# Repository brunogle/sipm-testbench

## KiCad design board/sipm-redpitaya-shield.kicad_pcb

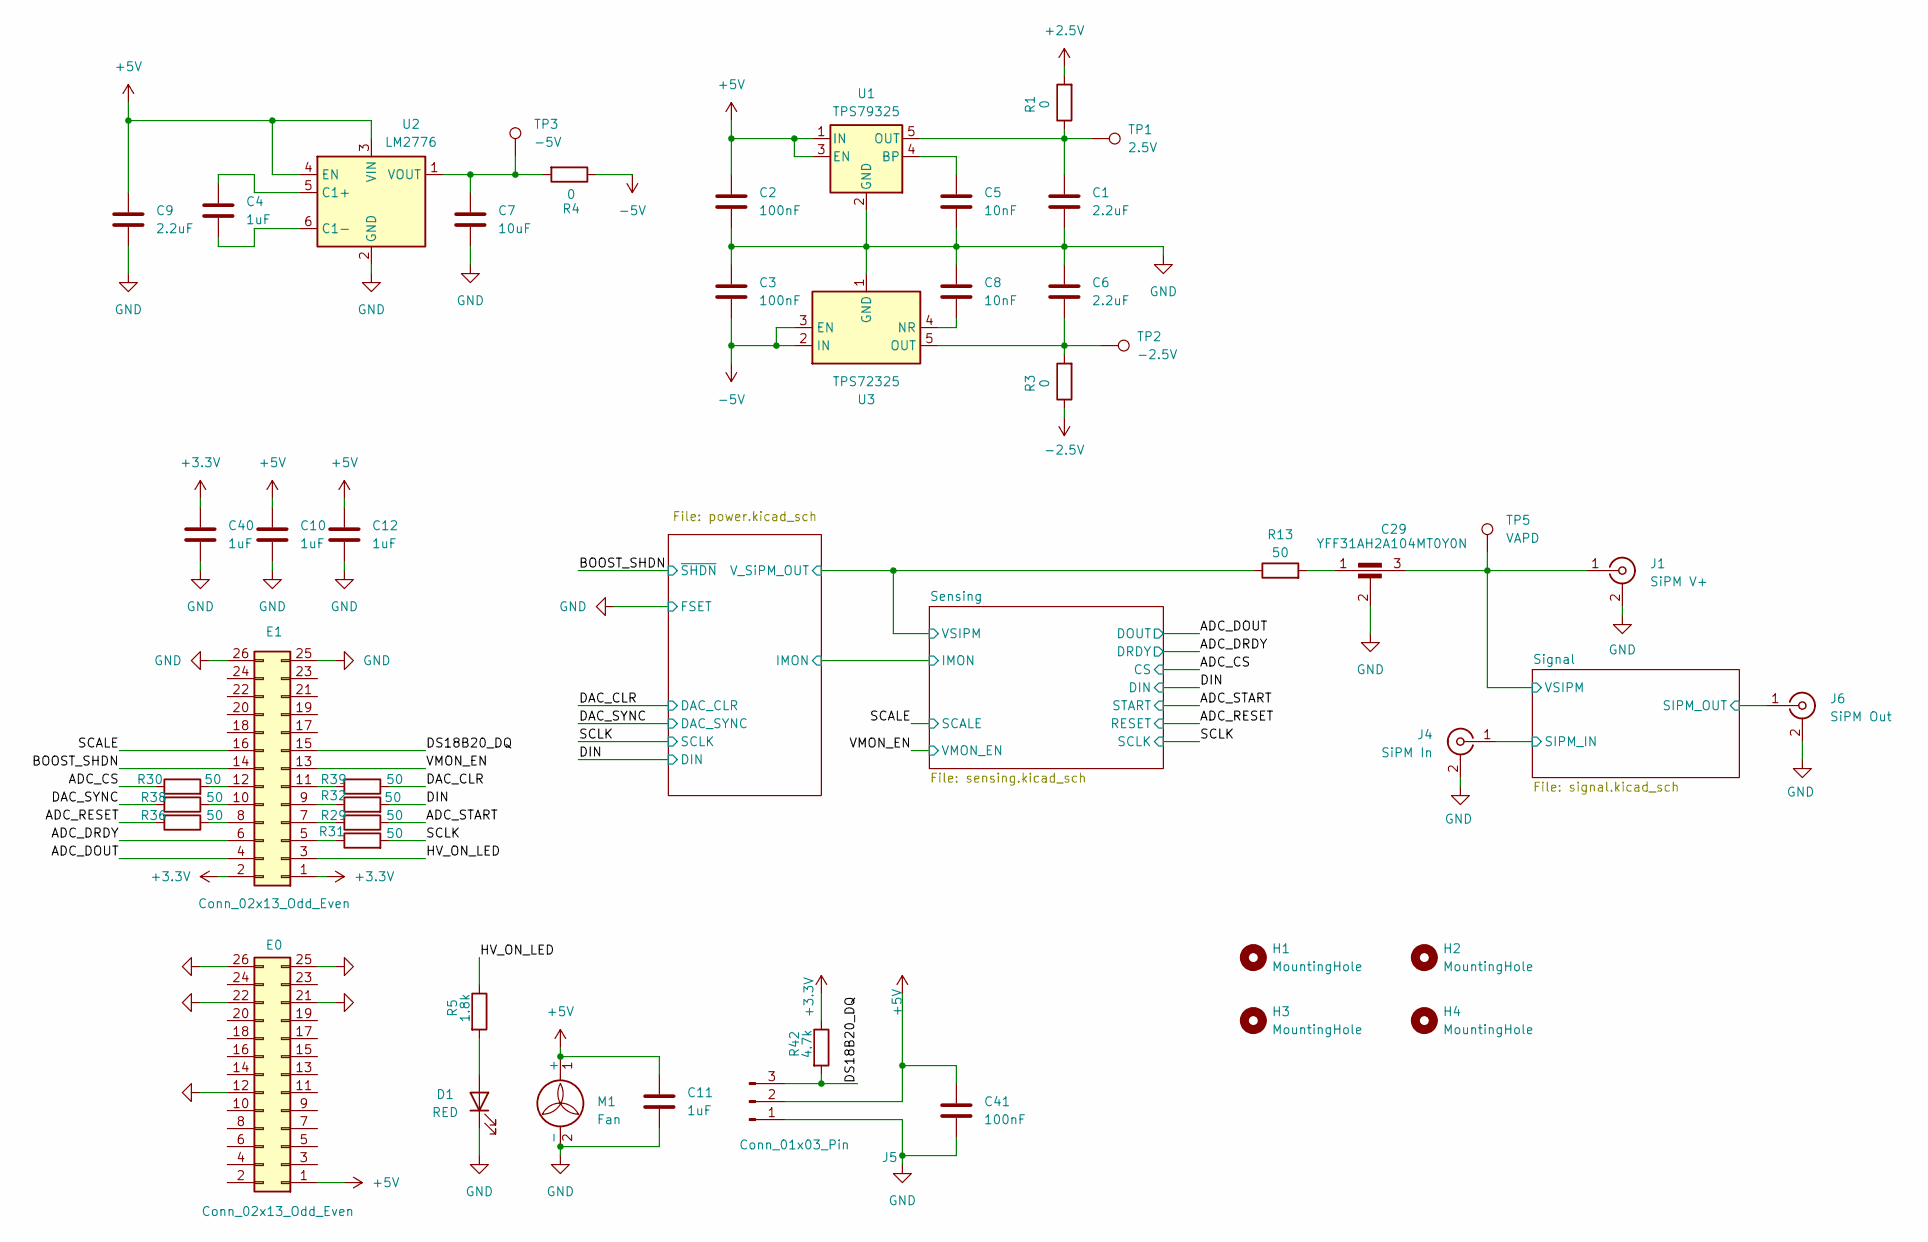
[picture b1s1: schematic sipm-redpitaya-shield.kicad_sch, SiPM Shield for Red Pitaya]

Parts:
C1, C6, C9: 2.2uF; C_0603_1608Metric
C2, C3, C41: 100nF; C_0603_1608Metric
C4, C10, C11, C12, C40: 1uF; C_0603_1608Metric
C5, C8: 10nF; C_0603_1608Metric
C7: 10uF; C_0603_1608Metric
C29: YFF31AH2A104MT0Y0N; YFF31HC
D1: RED; LED_0603_1608Metric_Pad1.05x0.95mm_HandSolder
E0, E1: Conn_02x13_Odd_Even; PinSocket_2x13_P2.54mm_Vertical
H1, H2, H3, H4: MountingHole; JLCPCB_ToolingHole
J1: SiPM V+; SMA_Samtec_SMA-J-P-H-ST-EM1_EdgeMount
J4: SiPM In; SMA_Samtec_SMA-J-P-H-ST-EM1_EdgeMount
J5: Conn_01x03_Pin; Molex_KK-254_AE-6410-03A_1x03_P2.54mm_Vertical
J6: SiPM Out; SMA_Samtec_SMA-J-P-H-ST-EM1_EdgeMount
M1: Fan; PinHeader_1x02_P2.54mm_Vertical
R1, R3, R4: 0; R_0603_1608Metric_Pad0.98x0.95mm_HandSolder
R5: 1.8k; R_0603_1608Metric
R13: 50; R_0603_1608Metric
R29, R30, R31, R32, R36, R38, R39: 50; R_0402_1005Metric
R42: 4.7k; R_0603_1608Metric
TP1: 2.5V; TestPoint_Pad_D1.0mm
TP2: -2.5V; TestPoint_Pad_D1.0mm
TP3: -5V; TestPoint_Pad_D1.0mm
TP5: VAPD; TestPoint_Pad_D1.0mm
U1: TPS79325; SOT-23-5
U2: LM2776; SOT-23-6
U3: TPS72325; SOT-23-5

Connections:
+2.5V: R1.2; also elsewhere on the board
+3.3V: C40.2, E1.1, E1.2, R42.1; also elsewhere on the board
+5V: C2.1, C9.1, C10.2, C11.1, C12.2, C41.2, E0.1, J5.2, M1.1 (+), U1.1 (IN), U1.3 (EN), U2.3 (VIN), U2.4 (EN); also elsewhere on the board
-2.5V: R3.1; also elsewhere on the board
-5V: C3.2, R4.1, U3.2 (IN), U3.3 (EN)
/ADC_CS: R30.1; also elsewhere on the board
/ADC_DOUT: E1.4; also elsewhere on the board
/ADC_DRDY: E1.6; also elsewhere on the board
/ADC_RESET: R36.2; also elsewhere on the board
/ADC_START: R29.1; also elsewhere on the board
/BOOST_SHDN: E1.14; also elsewhere on the board
/DAC_CLR: R39.1; also elsewhere on the board
/DAC_SYNC: R38.2; also elsewhere on the board
/DIN: R32.2; also elsewhere on the board
/DS18B20_DQ: E1.15, J5.3, R42.2
/HV_ON_LED: E1.3, R5.1
/Power/V_SiPM_OUT: R13.1; also elsewhere on the board
/SCALE: E1.16; also elsewhere on the board
/SCLK: R31.2; also elsewhere on the board
/Signal/SIPM_IN: J4.1 (In); also elsewhere on the board
/Signal/SIPM_OUT: J6.1 (In); also elsewhere on the board
/Signal/VSIPM: C29.3, J1.1 (In), TP5.1; also elsewhere on the board
/VMON_EN: E1.13; also elsewhere on the board
GND: C1.2, C2.2, C3.1, C5.2, C6.1, C7.2, C8.1, C9.2, C10.1, C11.2, C12.1, C29.2, C40.1, C41.1, D1.1 (K), E0.12, E0.21, E0.22, E0.25, E0.26, E1.25, E1.26, J1.2 (Ext), J4.2 (Ext), J5.1, J6.2 (Ext), M1.2 (-), U1.2 (GND), U2.2 (GND), U3.1 (GND); also elsewhere on the board
unnamed: C29.1, R13.2
unnamed: D1.2 (A), R5.2
unnamed: E1.5, R31.1
unnamed: E1.7, R29.2
unnamed: E1.8, R36.1
unnamed: E1.9, R32.1
unnamed: E1.10, R38.1
unnamed: E1.11, R39.2
unnamed: E1.12, R30.2
unnamed: C5.1, U1.4 (BP)
unnamed: C1.1, R1.1, TP1.1, U1.5 (OUT)
unnamed: C4.1, U2.5 (C1+)
unnamed: C4.2, U2.6 (C1-)
unnamed: C7.1, R4.2, TP3.1, U2.1 (VOUT)
unnamed: C8.2, U3.4 (NR)
unnamed: C6.2, R3.2, TP2.1, U3.5 (OUT)

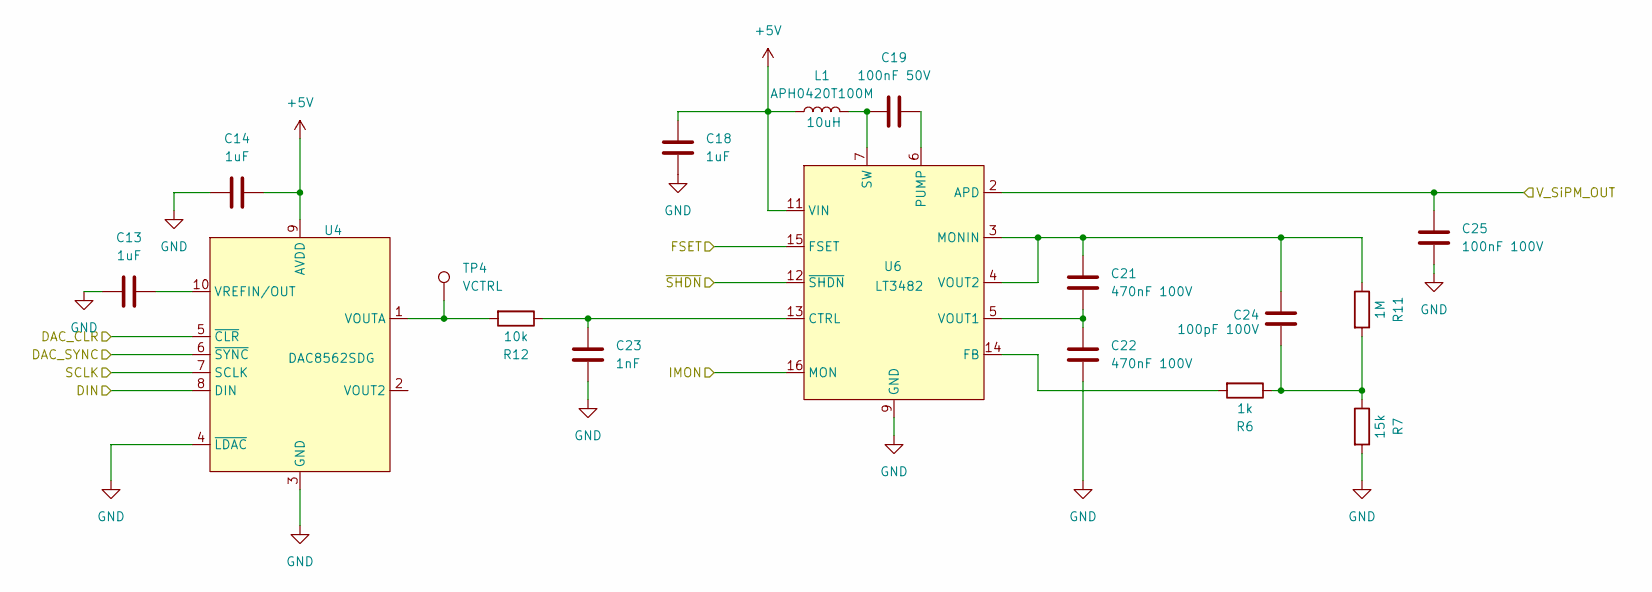
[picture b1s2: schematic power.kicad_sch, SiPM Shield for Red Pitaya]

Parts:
C13, C14, C18: 1uF; C_0603_1608Metric
C19: 100nF 50V; C_0603_1608Metric
C21, C22: 470nF 100V; C_1206_3216Metric
C23: 1nF; C_0603_1608Metric
C24: 100pF 100V; C_0603_1608Metric
C25: 100nF 100V; C_0805_2012Metric
L1: APH0420T100M; L_APV_APH0420
R6: 1k; R_0603_1608Metric
R7: 15k; R_0603_1608Metric
R11: 1M; R_0603_1608Metric
R12: 10k; R_0603_1608Metric
TP4: VCTRL; TestPoint_Pad_D1.0mm
U4: DAC8562SDG; VSSOP-10_3x3mm_P0.5mm
U6: LT3482; QFN-16-1EP_3x3mm_P0.5mm_EP1.45x1.45mm

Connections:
+5V: C14.2, C18.1, L1.1, U4.9 (AVDD), U6.11 (VIN); also elsewhere on the board
/BOOST_SHDN: U6.12 (~SHDN); also elsewhere on the board
/DAC_CLR: U4.5 (~CLR); also elsewhere on the board
/DAC_SYNC: U4.6 (~SYNC); also elsewhere on the board
/DIN: U4.8 (DIN); also elsewhere on the board
/Power/IMON: U6.16 (MON); also elsewhere on the board
/Power/V_SiPM_OUT: C25.1, U6.2 (APD); also elsewhere on the board
/SCLK: U4.7 (SCLK); also elsewhere on the board
GND: C13.2, C14.1, C18.2, C22.2, C23.1, C25.2, R7.2, U4.3 (GND), U4.4 (~LDAC), U6.9 (GND), U6.10 (GND), U6.15 (FSET), U6.17 (GND); also elsewhere on the board
unnamed: C19.2, L1.2, U6.7 (SW), U6.8 (SW)
unnamed: C24.2, R6.1, R7.1, R11.2
unnamed: R12.2, TP4.1, U4.1 (VOUTA)
unnamed: C13.1, U4.10 (VREFIN/OUT)
unnamed: C23.2, R12.1, U6.13 (CTRL)
unnamed: R6.2, U6.14 (FB)
unnamed: C21.1, C24.1, R11.1, U6.3 (MONIN), U6.4 (VOUT2)
unnamed: C19.1, U6.6 (PUMP)
unnamed: C21.2, C22.1, U6.5 (VOUT1)

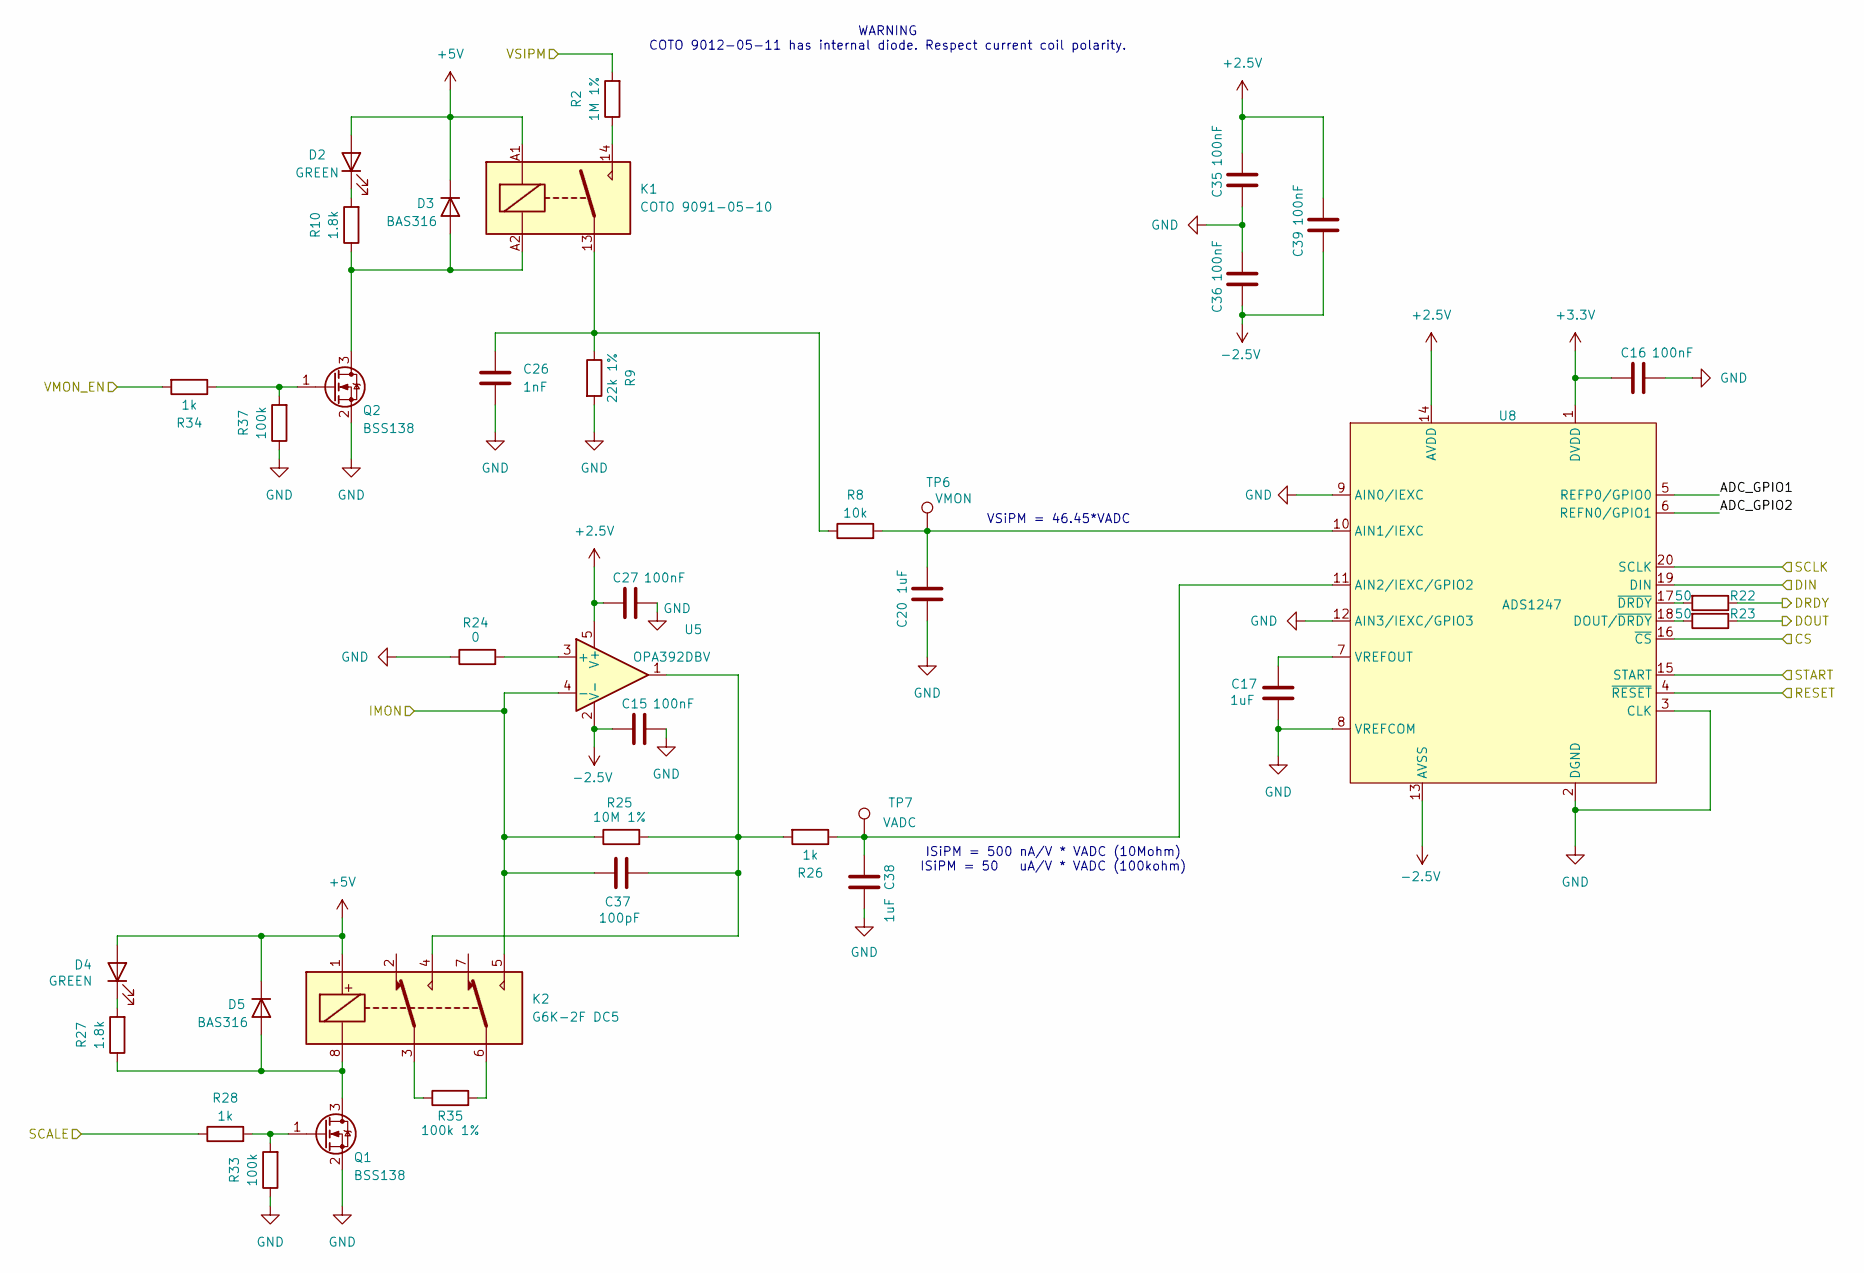
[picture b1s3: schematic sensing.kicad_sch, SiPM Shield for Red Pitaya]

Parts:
C15, C16, C27, C35, C36, C39: 100nF; C_0603_1608Metric
C17, C20, C38: 1uF; C_0603_1608Metric
C26: 1nF; C_0603_1608Metric
C37: 100pF; C_0603_1608Metric_Pad1.08x0.95mm_HandSolder
D2, D4: GREEN; LED_0603_1608Metric_Pad1.05x0.95mm_HandSolder
D3, D5: BAS316; D_SOD-323
K1: COTO 9091-05-10; Relay_SPST_COTO_9091
K2: G6K-2F DC5; Relay_DPDT_Omron_G6K-2F
Q1, Q2: BSS138; SOT-23
R2: 1M 1%; R_0603_1608Metric
R8: 10k; R_0603_1608Metric
R9: 22k 1%; R_0603_1608Metric
R10, R27: 1.8k; R_0603_1608Metric
R22, R23: 50; R_0603_1608Metric
R24: 0; R_0603_1608Metric_Pad0.98x0.95mm_HandSolder
R25: 10M 1%; R_0603_1608Metric_Pad0.98x0.95mm_HandSolder
R26: 1k; R_0603_1608Metric
R28, R34: 1k; R_0402_1005Metric
R33, R37: 100k; R_0402_1005Metric
R35: 100k 1%; R_0603_1608Metric_Pad0.98x0.95mm_HandSolder
TP6: VMON; TestPoint_Pad_D1.0mm
TP7: VADC; TestPoint_Pad_D1.0mm
U5: OPA392DBV; SOT-23-5
U8: ADS1247; TSSOP-20_4.4x6.5mm_P0.65mm

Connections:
+2.5V: C27.1, C35.2, C39.2, U5.5 (V+), U8.14 (AVDD); also elsewhere on the board
+3.3V: C16.1, U8.1 (DVDD); also elsewhere on the board
+5V: D2.2 (A), D3.1 (K), D4.2 (A), D5.1 (K), K1.A1, K2.1; also elsewhere on the board
-2.5V: C15.1, C36.1, C39.1, U5.2 (V-), U8.13 (AVSS); also elsewhere on the board
/ADC_CS: U8.16 (~CS); also elsewhere on the board
/ADC_DOUT: R23.1; also elsewhere on the board
/ADC_DRDY: R22.1; also elsewhere on the board
/ADC_RESET: U8.4 (~RESET); also elsewhere on the board
/ADC_START: U8.15 (START); also elsewhere on the board
/DIN: U8.19 (DIN); also elsewhere on the board
/Power/IMON: C37.2, K2.5, R25.1, U5.4 (-); also elsewhere on the board
/Power/V_SiPM_OUT: R2.2; also elsewhere on the board
/SCALE: R28.1; also elsewhere on the board
/SCLK: U8.20 (SCLK); also elsewhere on the board
/Sensing/ADC_GPIO1: U8.5 (REFP0/GPIO0)
/Sensing/ADC_GPIO2: U8.6 (REFN0/GPIO1)
/VMON_EN: R34.2; also elsewhere on the board
GND: C15.2, C16.2, C17.1, C20.1, C26.2, C27.2, C35.1, C36.2, C38.2, Q1.2 (S), Q2.2 (S), R9.2, R24.1, R33.1, R37.1, U8.2 (DGND), U8.3 (CLK), U8.8 (VREFCOM), U8.9 (AIN0/IEXC), U8.12 (AIN3/IEXC/GPIO3); also elsewhere on the board
unnamed: C26.1, K1.13, R8.1, R9.1
unnamed: C37.1, K2.4, R25.2, R26.2, U5.1
unnamed: D2.1 (K), R10.2
unnamed: D3.2 (A), K1.A2, Q2.3 (D), R10.1
unnamed: D4.1 (K), R27.2
unnamed: D5.2 (A), K2.8, Q1.3 (D), R27.1
unnamed: K1.14, R2.1
unnamed: K2.3, R35.1
unnamed: K2.6, R35.2
unnamed: Q1.1 (G), R28.2, R33.2
unnamed: Q2.1 (G), R34.1, R37.2
unnamed: R24.2, U5.3 (+)
unnamed: C20.2, R8.2, TP6.1, U8.10 (AIN1/IEXC)
unnamed: C38.1, R26.1, TP7.1, U8.11 (AIN2/IEXC/GPIO2)
unnamed: R23.2, U8.18 (DOUT/~DRDY)
unnamed: C17.2, U8.7 (VREFOUT)
unnamed: R22.2, U8.17 (~DRDY)

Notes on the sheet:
ISiPM = 500 nA/V * VADC (10Mohm) ISiPM = 50 uA/V * VADC (100kohm)
VSiPM = 46.45*VADC
WARNING COTO 9012-05-11 has internal diode. Respect current coil polarity.

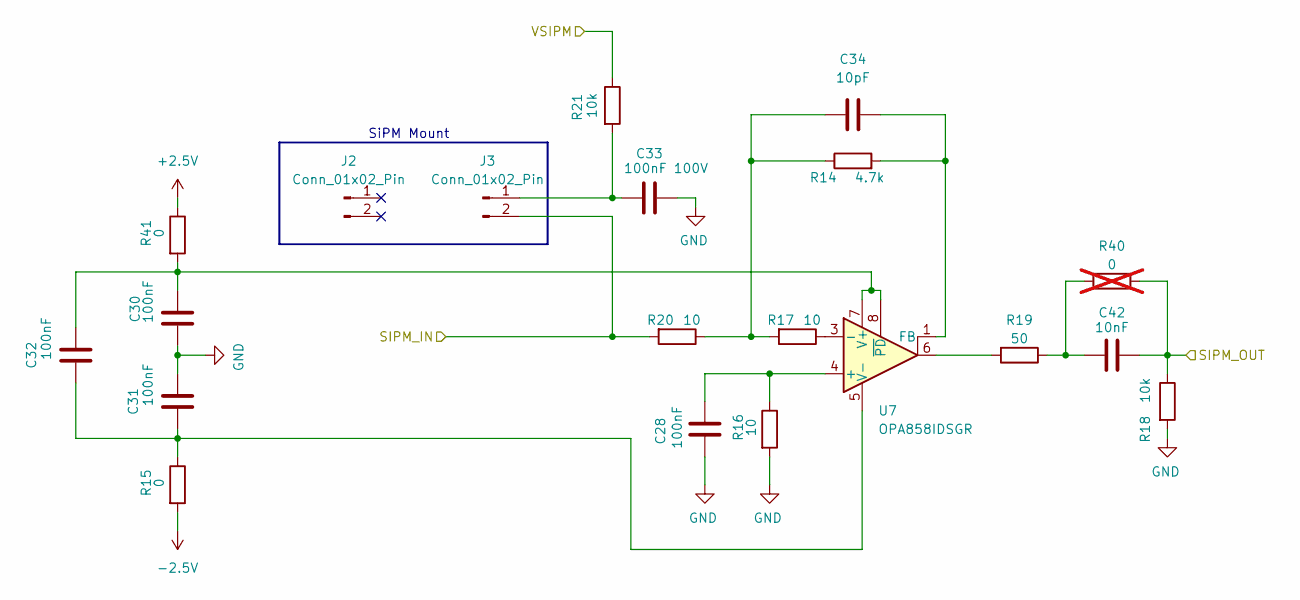
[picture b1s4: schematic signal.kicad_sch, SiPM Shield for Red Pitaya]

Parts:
C28, C30, C31, C32: 100nF; C_0603_1608Metric
C33: 100nF 100V; C_0805_2012Metric
C34: 10pF; C_0402_1005Metric_Pad0.74x0.62mm_HandSolder
C42: 10nF; C_0603_1608Metric
J2, J3: Conn_01x02_Pin; PinSocket_1x02_P2.54mm_Vertical
R14: 4.7k; R_0402_1005Metric_Pad0.72x0.64mm_HandSolder
R15, R41: 0; R_0603_1608Metric_Pad0.98x0.95mm_HandSolder
R16: 10; R_0603_1608Metric
R17, R20: 10; R_0402_1005Metric_Pad0.72x0.64mm_HandSolder
R18, R21: 10k; R_0603_1608Metric
R19: 50; R_0603_1608Metric
R40: 0; R_0603_1608Metric; not fitted
U7: OPA858IDSGR; WSON-8-1EP_2x2mm_P0.5mm_EP0.9x1.6mm

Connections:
+2.5V: R41.1; also elsewhere on the board
-2.5V: R15.2; also elsewhere on the board
/Signal/SIPM_IN: J3.2, R20.2; also elsewhere on the board
/Signal/SIPM_OUT: C42.2, R18.1, R40.1; also elsewhere on the board
/Signal/VSIPM: R21.1; also elsewhere on the board
GND: C28.1, C30.1, C31.2, C33.2, R16.2, R18.2; also elsewhere on the board
unnamed: C31.1, C32.1, R15.1, U7.5 (V-), U7.9 (V-)
unnamed: C34.1, R14.1, R17.2, R20.1
unnamed: C42.1, R19.1, R40.2
unnamed: C33.1, J3.1, R21.2
unnamed: R19.2, U7.6
unnamed: C28.2, R16.1, U7.4 (+)
unnamed: R17.1, U7.3 (-)
unnamed: C34.2, R14.2, U7.1 (FB)
unnamed: C30.2, C32.2, R41.2, U7.7 (V+), U7.8 (~PD)

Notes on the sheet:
SiPM Mount

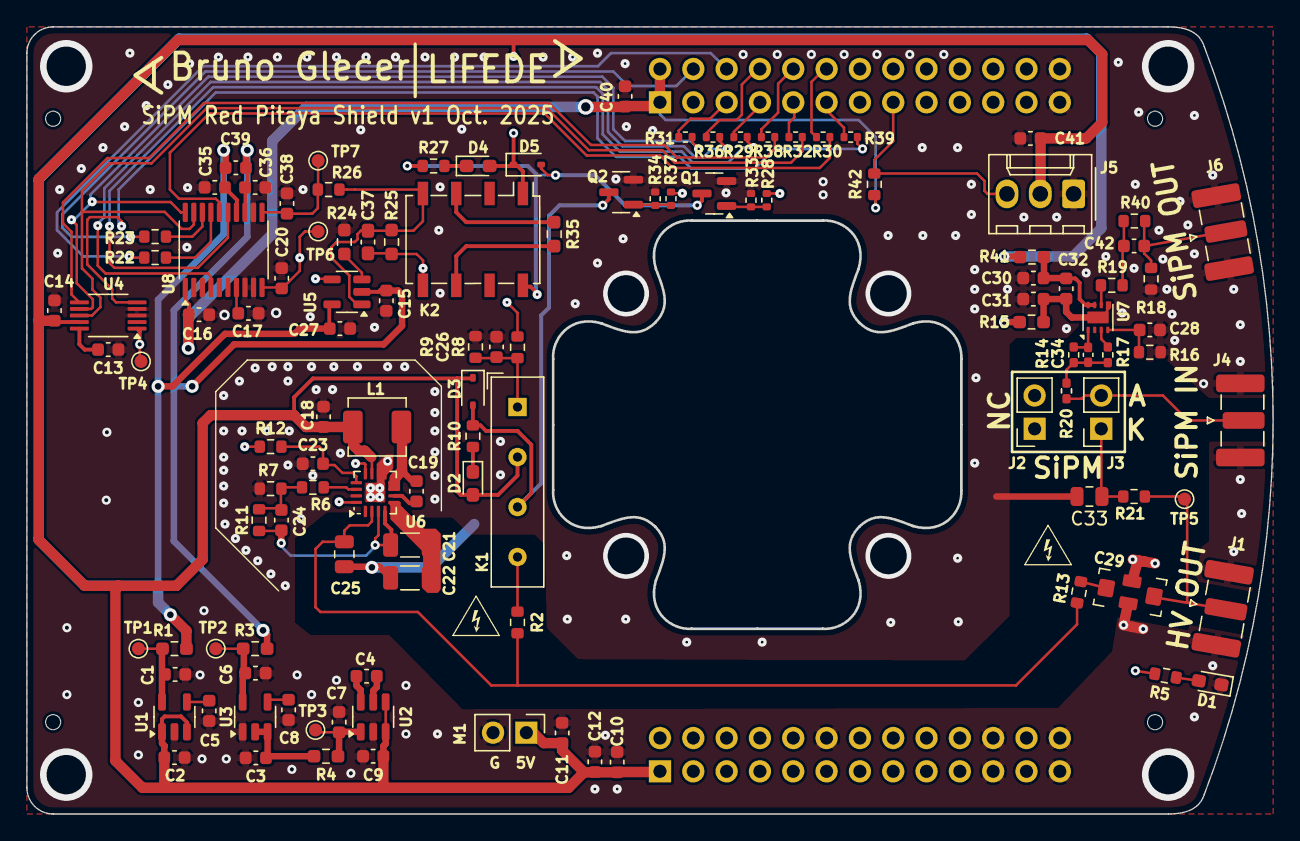
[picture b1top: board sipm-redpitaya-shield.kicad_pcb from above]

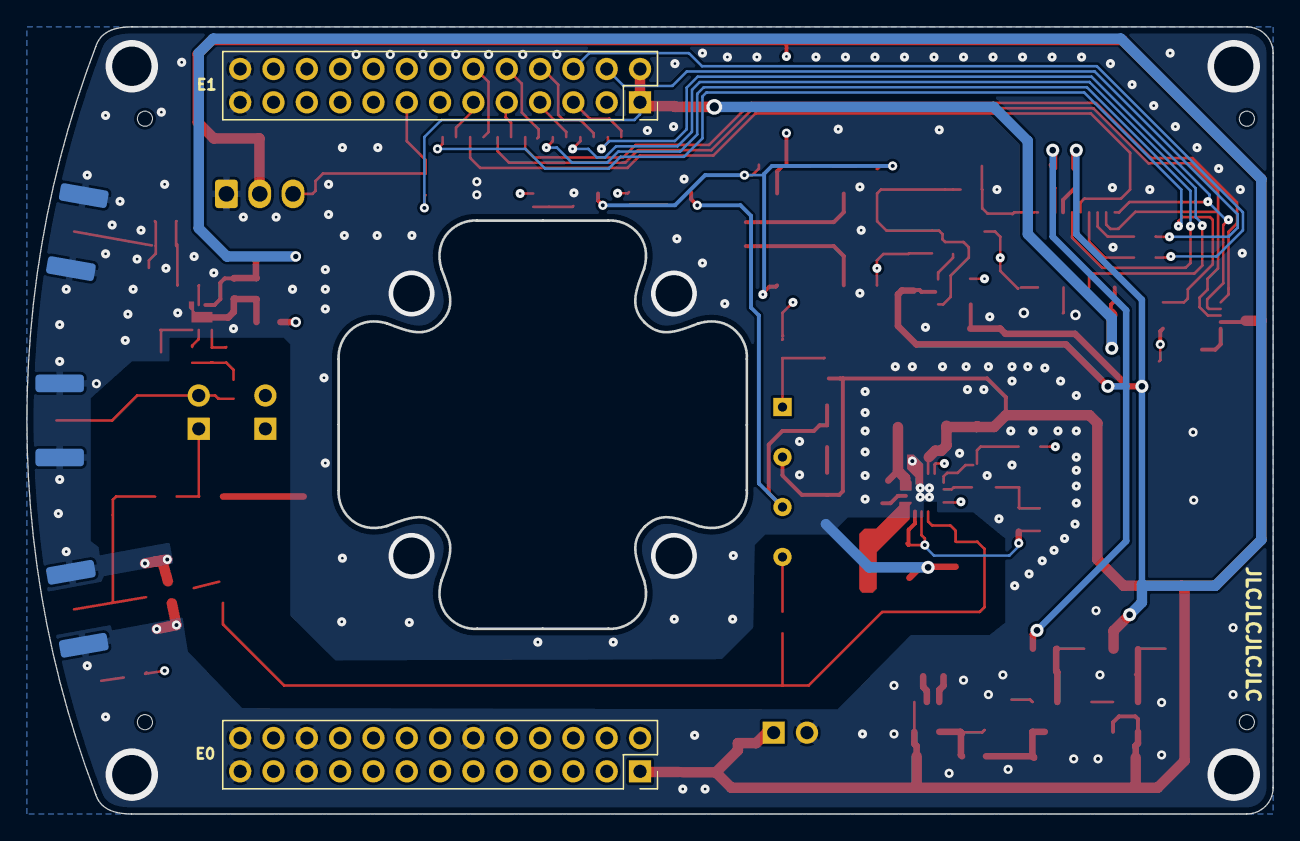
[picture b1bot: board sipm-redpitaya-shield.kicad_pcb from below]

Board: 4 copper layers, 94.9 x 59.9 mm, 122 parts (2 on the bottom side), 76 nets.

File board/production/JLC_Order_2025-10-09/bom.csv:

Designator,Footprint,Quantity,Value,LCSC Part #
"C1, C6, C9",0603,3,2.2uF,
"C10, C11, C12, C13, C14, C17, C18, C20, C38, C4, C40",0603,11,1uF,
"C15, C16, C2, C27, C28, C3, C30, C31, C32, C35, C36, C39, C41",0603,13,100nF,
C19,0603,1,100nF 50V,
"C21, C22",1206,2,470nF 100V,
"C23, C26",0603,2,1nF,
C24,0603,1,100pF 100V,
"C25, C33",0805,2,100nF 100V,
C29,YFF31HC,1,YFF31AH2A104MT0Y0N,
C34,0402,1,10pF,
C37,0603,1,100pF,
"C42, C5, C8",0603,3,10nF,
C7,0603,1,10uF,
D1,0603,1,RED,
"D2, D4",0603,2,GREEN,
"D3, D5",D_SOD-323,2,BAS316,
"E0, E1",PinSocket_2x13_P2.54mm_Vertical,2,Conn_02x13_Odd_Even,
J1,SMA_Samtec_SMA-J-P-H-ST-EM1_EdgeMount,1,SiPM V+,
"J2, J3",PinSocket_1x02_P2.54mm_Vertical,2,Conn_01x02_Pin,
J4,SMA_Samtec_SMA-J-P-H-ST-EM1_EdgeMount,1,SiPM In,
J5,Molex_KK-254_AE-6410-03A_1x03_P2.54mm_Vertical,1,Conn_01x03_Pin,
J6,SMA_Samtec_SMA-J-P-H-ST-EM1_EdgeMount,1,SiPM Out,
K1,Relay_SPST_COTO_9091,1,COTO 9091-05-10,
K2,Relay_DPDT_Omron_G6K-2F,1,G6K-2F,
L1,L_APV_APH0420,1,APH0420T100M,
M1,PinHeader_1x02_P2.54mm_Vertical,1,Fan,
"Q1, Q2",SOT-23,2,BSS138,
"R1, R15, R24, R3, R4, R41",0603,6,0,
"R10, R27, R5",0603,3,1.8k,
R11,0603,1,1M,
"R12, R18, R21, R8",0603,4,10k,
"R13, R19, R22, R23",0603,4,50,
R14,0402,1,4.7k,
R16,0603,1,10,
"R17, R20",0402,2,10,
R2,0603,1,1M  1%,
R25,0603,1,10M 1%,
"R26, R6",0603,2,1k,
"R28, R34",0402,2,1k,
"R29, R30, R31, R32, R36, R38, R39",0402,7,50,
"R33, R37",0402,2,100k,
R35,0603,1,100k 1%,
R42,0603,1,4.7k,
R7,0603,1,15k,
R9,0603,1,22k  1%,
U1,SOT-23-5,1,TPS79325,
U2,SOT-23-6,1,LM2776,
U3,SOT-23-5,1,TPS72325,
U4,VSSOP-10_3x3mm_P0.5mm,1,DAC8562SDG,
U5,SOT-23-5,1,OPA392DBV,
U6,QFN-16-1EP_3x3mm_P0.5mm_EP1.45x1.45mm,1,LT3482,
U7,WSON-8-1EP_2x2mm_P0.5mm_EP0.9x1.6mm,1,OPA858IDSGR,
U8,TSSOP-20_4.4x6.5mm_P0.65mm,1,ADS1247,

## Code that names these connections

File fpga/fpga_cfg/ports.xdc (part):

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set_property IOSTANDARD LVCMOS33 [get_ports DIN]
set_property SLEW FAST [get_ports DIN]
set_property DRIVE 8 [get_ports DIN]
set_property PACKAGE_PIN K17 [get_ports DIN]

set_property IOSTANDARD LVCMOS33 [get_ports SCLK]
set_property SLEW FAST [get_ports SCLK]
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set_property IOSTANDARD LVCMOS33 [get_ports DAC_SYNC]
set_property SLEW FAST [get_ports DAC_SYNC]
set_property DRIVE 8 [get_ports DAC_SYNC]
set_property PACKAGE_PIN K18 [get_ports DAC_SYNC]

set_property IOSTANDARD LVCMOS33 [get_ports BOOST_SHDN]
set_property SLEW FAST [get_ports BOOST_SHDN]
set_property DRIVE 8 [get_ports BOOST_SHDN]
set_property PACKAGE_PIN L17 [get_ports BOOST_SHDN]

set_property IOSTANDARD LVCMOS33 [get_ports BOOST_SHDN]
set_property SLEW FAST [get_ports BOOST_SHDN]
set_property DRIVE 8 [get_ports BOOST_SHDN]
set_property PACKAGE_PIN L17 [get_ports BOOST_SHDN]

set_property IOSTANDARD LVCMOS33 [get_ports DAC_CLR]
set_property SLEW FAST [get_ports DAC_CLR]
set_property DRIVE 8 [get_ports DAC_CLR]
set_property PACKAGE_PIN L14 [get_ports DAC_CLR]

set_property IOSTANDARD LVCMOS33 [get_ports SCALE]
set_property SLEW FAST [get_ports SCALE]
set_property DRIVE 8 [get_ports SCALE]
set_property PACKAGE_PIN J16 [get_ports SCALE]

set_property IOSTANDARD LVCMOS33 [get_ports DOUT]
set_property SLEW FAST [get_ports DOUT]
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set_property IOSTANDARD LVCMOS33 [get_ports HV_ON_LED]
set_property SLEW FAST [get_ports HV_ON_LED]
set_property DRIVE 8 [get_ports HV_ON_LED]
set_property PACKAGE_PIN G17 [get_ports HV_ON_LED]

set_property IOSTANDARD LVCMOS33 [get_ports ADC_CS]
set_property SLEW FAST [get_ports ADC_CS]
set_property DRIVE 8 [get_ports ADC_CS]
set_property PACKAGE_PIN L15 [get_ports ADC_CS]

set_property IOSTANDARD LVCMOS33 [get_ports ADC_DRDY]
set_property SLEW FAST [get_ports ADC_DRDY]
set_property DRIVE 8 [get_ports ADC_DRDY]
set_property PACKAGE_PIN H17 [get_ports ADC_DRDY]

set_property IOSTANDARD LVCMOS33 [get_ports ADC_RESET]
set_property SLEW FAST [get_ports ADC_RESET]
set_property DRIVE 8 [get_ports ADC_RESET]
set_property PACKAGE_PIN H18 [get_ports ADC_RESET]

set_property IOSTANDARD LVCMOS33 [get_ports ADC_START]
set_property SLEW FAST [get_ports ADC_START]
set_property DRIVE 8 [get_ports ADC_START]
set_property PACKAGE_PIN J18 [get_ports ADC_START]

set_property IOSTANDARD LVCMOS33 [get_ports VMON_EN]
set_property SLEW FAST [get_ports VMON_EN]
set_property DRIVE 8 [get_ports VMON_EN]
set_property PACKAGE_PIN L16 [get_ports VMON_EN]

### SATA connector

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
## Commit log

2025-09-20 Signal gen to DMA working. (raw sampling)
2025-09-24 Basic trap filter, needs testing
2025-10-21 Only SPI Test
2025-10-22 Extended GPIO + SPI
2025-10-23 SPI & DMA working
2025-10-24 SPI Updated
2025-10-30 ADC Working
2025-10-31 Started histogram
2025-10-31 Working histogram module
2025-10-31 Testing trapezoid filter + peak + hist
2025-11-03 All basic functionality working
2025-12-05 Added soft+board
2026-02-20 Added scripts for presentation
